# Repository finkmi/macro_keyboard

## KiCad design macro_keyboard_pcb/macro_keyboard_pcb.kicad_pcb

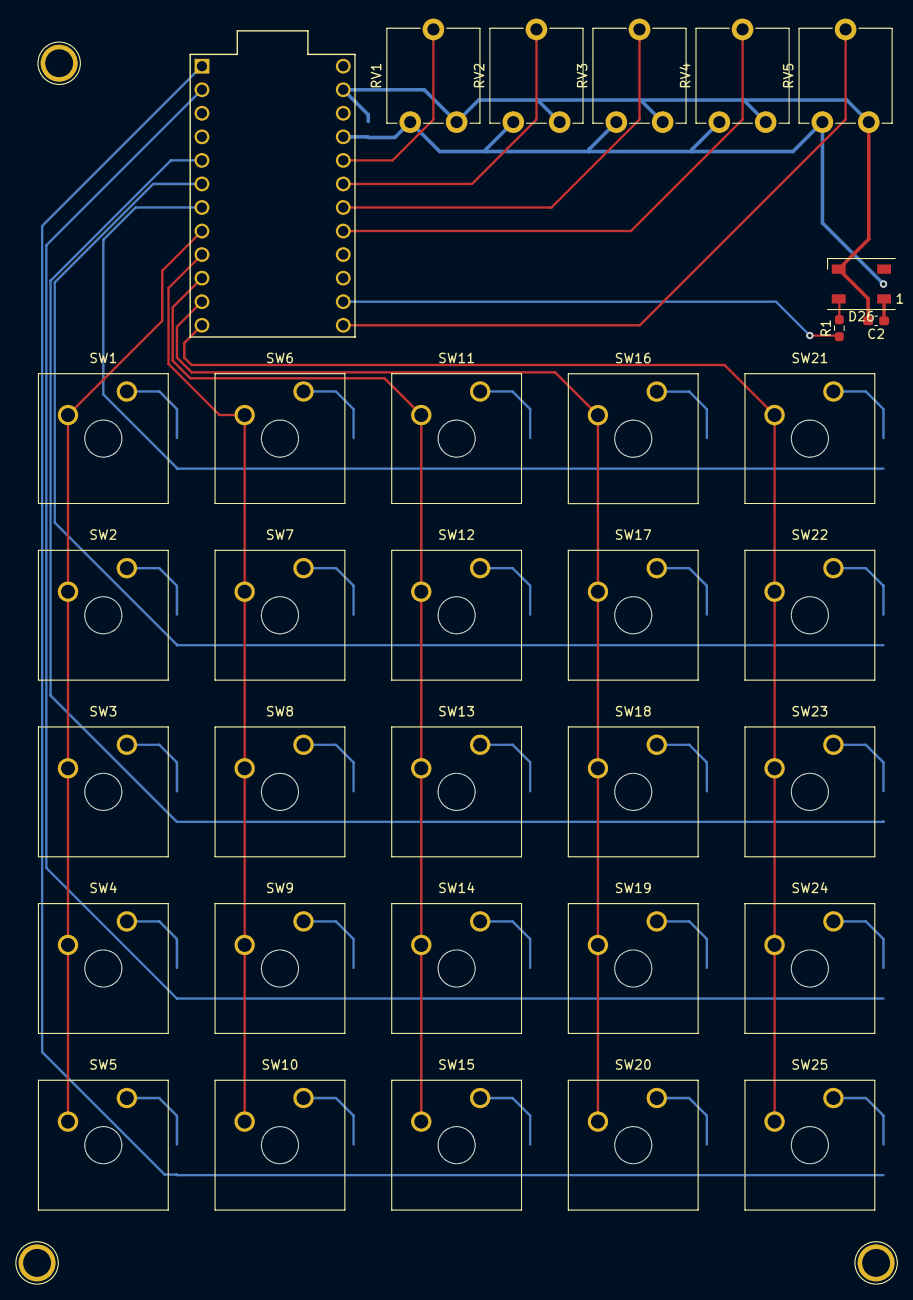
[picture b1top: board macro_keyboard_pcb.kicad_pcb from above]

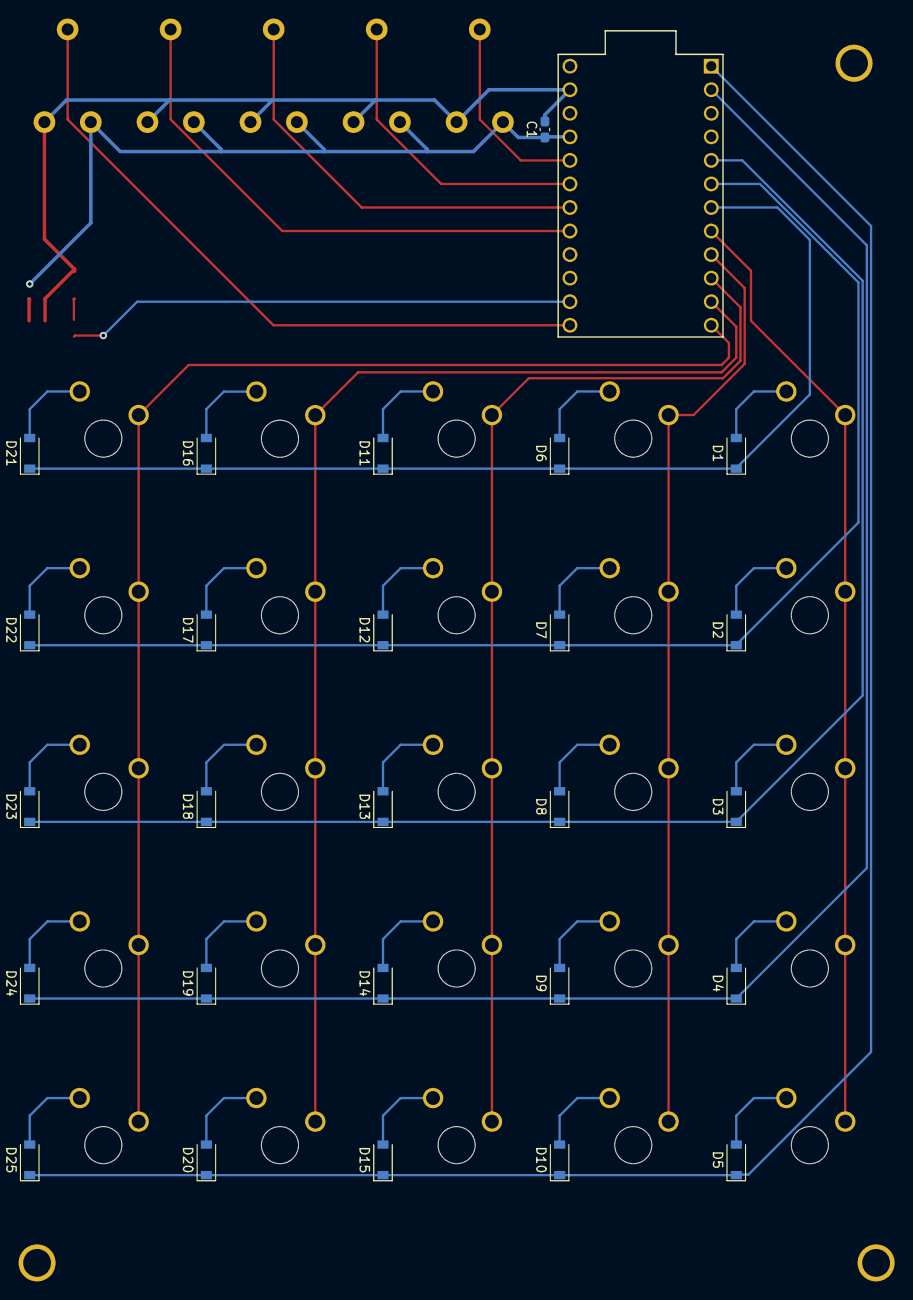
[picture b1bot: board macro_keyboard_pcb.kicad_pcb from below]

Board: 2 copper layers, 63 parts (26 on the bottom side), 44 nets.

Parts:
 : TestPoint_Plated_Hole_D3.0mm
 #2,  #3: TestPoint_Plated_Hole_D3.0mm
C1, C2: C_Small; C_0603_1608Metric_Pad1.08x0.95mm_HandSolder
D1, D2, D3, D4, D5, D6, D7, D8, D9, D10, D11, D12, D13, D14, D15, D16, D17, D18, D19, D20, D21, D22, D23, D24, D25: 1N4148; D_SOD-123
D26: WS2812B; LED_WS2812B_PLCC4_5.0x5.0mm_P3.2mm
R1: 360; R_0603_1608Metric_Pad0.98x0.95mm_HandSolder
RV1, RV2, RV3, RV4, RV5: R_POT; Potentiometer_ACP_CA9-V10_Vertical
SW1, SW2, SW3, SW4, SW5, SW6, SW7, SW8, SW9, SW10, SW11, SW12, SW13, SW14, SW15, SW16, SW17, SW18, SW19, SW20, SW21, SW22, SW23, SW24, SW25: CherryMX; CherryMX_1.00u
U1: ProMicro

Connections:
+5V: C1.1, C2.1, D26.1, RV1.3, RV2.3, RV3.3, RV4.3, RV5.3, U1.21
COL0: SW1.1, SW2.1, SW3.1, SW4.1, SW5.1, U1.8
COL1: SW6.1, SW7.1, SW8.1, SW9.1, SW10.1, U1.9
COL2: SW11.1, SW12.1, SW13.1, SW14.1, SW15.1, U1.10
COL3: SW16.1, SW17.1, SW18.1, SW19.1, SW20.1, U1.11
COL4: SW21.1, SW22.1, SW23.1, SW24.1, SW25.1, U1.12
GND: C1.2, C2.2, D26.3, RV1.1, RV2.1, RV3.1, RV4.1, RV5.1, U1.23
LED_DATA: R1.1, U1.14
unnamed: D1.2, SW1.2
unnamed: D2.2, SW2.2
unnamed: D3.2, SW3.2
unnamed: D4.2, SW4.2
unnamed: D5.2, SW5.2
unnamed: D6.2, SW6.2
unnamed: D7.2, SW7.2
unnamed: D8.2, SW8.2
unnamed: D9.2, SW9.2
unnamed: D10.2, SW10.2
unnamed: D11.2, SW11.2
unnamed: D12.2, SW12.2
unnamed: D13.2, SW13.2
unnamed: D14.2, SW14.2
unnamed: D15.2, SW15.2
unnamed: D16.2, SW16.2
unnamed: D17.2, SW17.2
unnamed: D18.2, SW18.2
unnamed: D19.2, SW19.2
unnamed: D20.2, SW20.2
unnamed: D21.2, SW21.2
unnamed: D22.2, SW22.2
unnamed: D23.2, SW23.2
unnamed: D24.2, SW24.2
unnamed: D25.2, SW25.2
unnamed: D26.4, R1.2
POT0: RV1.2, U1.20
POT1: RV2.2, U1.19
POT2: RV3.2, U1.18
POT3: RV4.2, U1.17
POT4: RV5.2, U1.13
ROW0: D1.1, D6.1, D11.1, D16.1, D21.1, U1.7
ROW1: D2.1, D7.1, D12.1, D17.1, D22.1, U1.6
ROW2: D3.1, D8.1, D13.1, D18.1, D23.1, U1.5
ROW3: D4.1, D9.1, D14.1, D19.1, D24.1, U1.2
ROW4: D5.1, D10.1, D15.1, D20.1, D25.1, U1.1

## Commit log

2020-11-20 Create kicad projects with empty pcb and sch files
2020-11-20 Add submodules for pro micro and cherry mx switches
2020-11-20 Add more submodules
2020-11-20 Remove unecessary libs and add in working ones for cherry swithces. Make first draft of schematic
2020-11-21 Add LED circuit, assign footprints
2020-11-22 WIP adding routes
2020-11-22 First draft of routes
2020-11-22 add mounting holes
2020-11-22 Add silkscreen and generate gerber and drill files
2020-11-22 Add board edge lines and dimensions, regenerated gerber files
